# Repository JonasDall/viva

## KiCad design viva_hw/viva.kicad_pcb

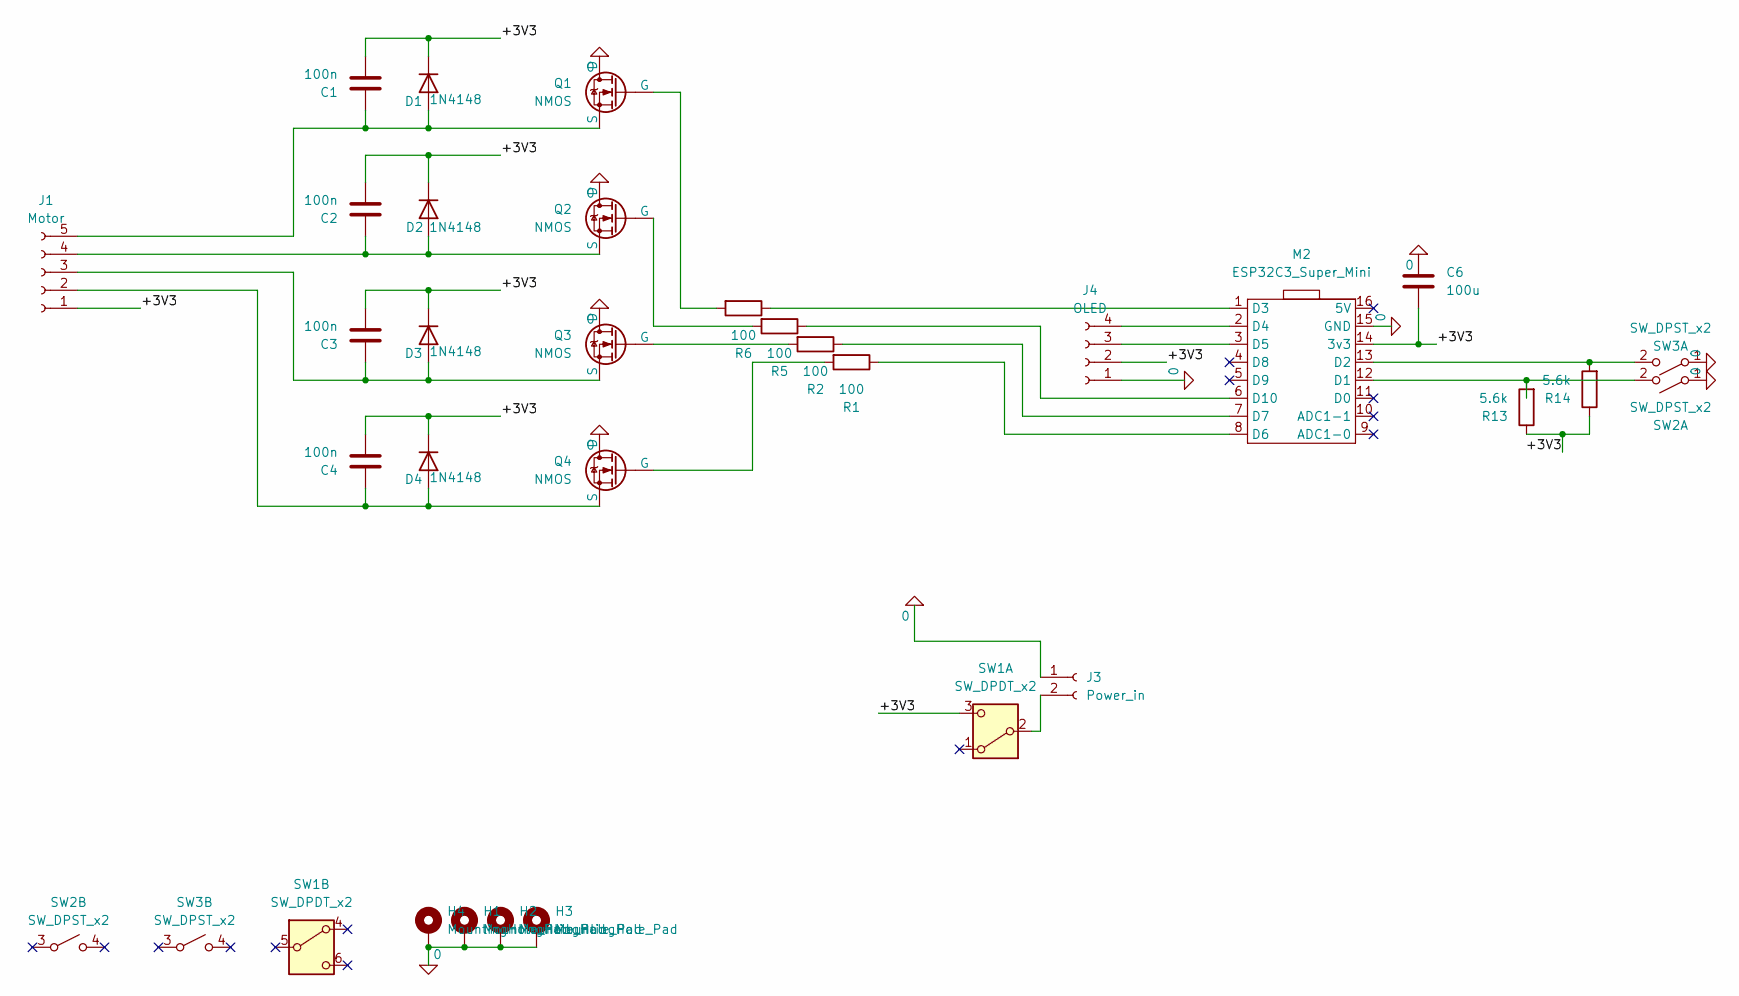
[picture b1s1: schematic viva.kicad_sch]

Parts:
C1, C2, C3, C4: 100n; C_Disc_D4.3mm_W1.9mm_P5.00mm
C6: 100u; CP_Radial_D8.0mm_P3.50mm
D1, D2, D3, D4: 1N4148; D_DO-34_SOD68_P7.62mm_Horizontal
H1, H2, H3, H4: MountingHole_Pad; MountingHole_3.2mm_M3_ISO7380_Pad
J1: Motor; PinHeader_1x05_P2.54mm_Vertical
J3: Power_in; Barrel_Plug_5.5mmx2.1mm
J4: OLED; OLED_0.96
M2: ESP32C3_Super_Mini; ESP32C3_SUPER_MINI_THR
Q1, Q2, Q3, Q4: NMOS; TO-92L_Inline
R1, R2, R5, R6: 100; R_Axial_DIN0207_L6.3mm_D2.5mm_P10.16mm_Horizontal
R13, R14: 5.6k; R_Axial_DIN0207_L6.3mm_D2.5mm_P10.16mm_Horizontal
SW1: SW_DPDT_x2; SK-22D07G4
SW2, SW3: SW_DPST_x2; TACTILE-2P-THT

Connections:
0: C6.2, H1.1, H2.1, H3.1, H4.1, J3.1, J4.1, M2.15 (GND), Q1.1 (D), Q2.1 (D), Q3.1 (D), Q4.1 (D), SW2.1 (A), SW3.1 (A)
/+3V3: C1.1, C2.1, C3.1, C4.1, C6.1, D1.1 (K), D2.1 (K), D3.1 (K), D4.1 (K), J1.1, J4.2, M2.14 (3v3), R13.1, R14.1, SW1.3 (C)
unnamed: C1.2, D1.2 (A), J1.5, Q1.3 (S)
unnamed: C2.2, D2.2 (A), J1.4, Q2.3 (S)
unnamed: C3.2, D3.2 (A), J1.3, Q3.3 (S)
unnamed: C4.2, D4.2 (A), J1.2, Q4.3 (S)
unnamed: J3.2, SW1.2 (B)
unnamed: J4.3, M2.3 (D5)
unnamed: J4.4, M2.2 (D4)
unnamed: M2.12 (D1), R13.2, SW2.2 (B)
unnamed: M2.13 (D2), R14.2, SW3.2 (B)
unnamed: M2.1 (D3), R6.1
unnamed: M2.8 (D6), R1.1
unnamed: M2.7 (D7), R2.1
unnamed: M2.6 (D10), R5.1
unnamed: Q1.2 (G), R6.2
unnamed: Q2.2 (G), R5.2
unnamed: Q3.2 (G), R2.2
unnamed: Q4.2 (G), R1.2

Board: 2 copper layers, 30 parts (0 on the bottom side), 19 nets, no tracks yet.

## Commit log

2026-01-16 feat: init commit
2026-01-26 feat: added lcd screen
2026-01-26 feat: screen working
2026-02-08 feat: added hw folder
2026-02-08 feat: updated footprints
2026-02-09 feat: changed socket size for display
2026-02-09 feat: began emg work
2026-02-09 feat: spec update
2026-02-11 feat: added emg circuit
2026-02-11 feat: added backup
2026-02-14 feat: backup
2026-02-14 feat: added sallen key filters
2026-02-15 feat: began pcb work
2026-02-15 feat: cleaned up backup files
2026-04-21 feat: added switches to schematic, created simulation sheet
2026-04-21 feat: added simulations
2026-04-26 feat: emg progress
2026-04-29 feat: removed analog
2026-05-04 feat: dont remember
2026-05-04 feat: successfully tested control circuit
2026-05-05 feat: finished schematic
2026-05-06 feat: completed v_1
2026-05-06 feat: began print work
2026-05-07 feat: body done
2026-05-10 feat: box complete
2026-05-10 feat: adjusted lid
2026-05-13 feat: updated stl files
2026-05-13 feat: added pattern files
2026-05-18 feat: program complete
2026-06-05 feat: v2, changed controller
